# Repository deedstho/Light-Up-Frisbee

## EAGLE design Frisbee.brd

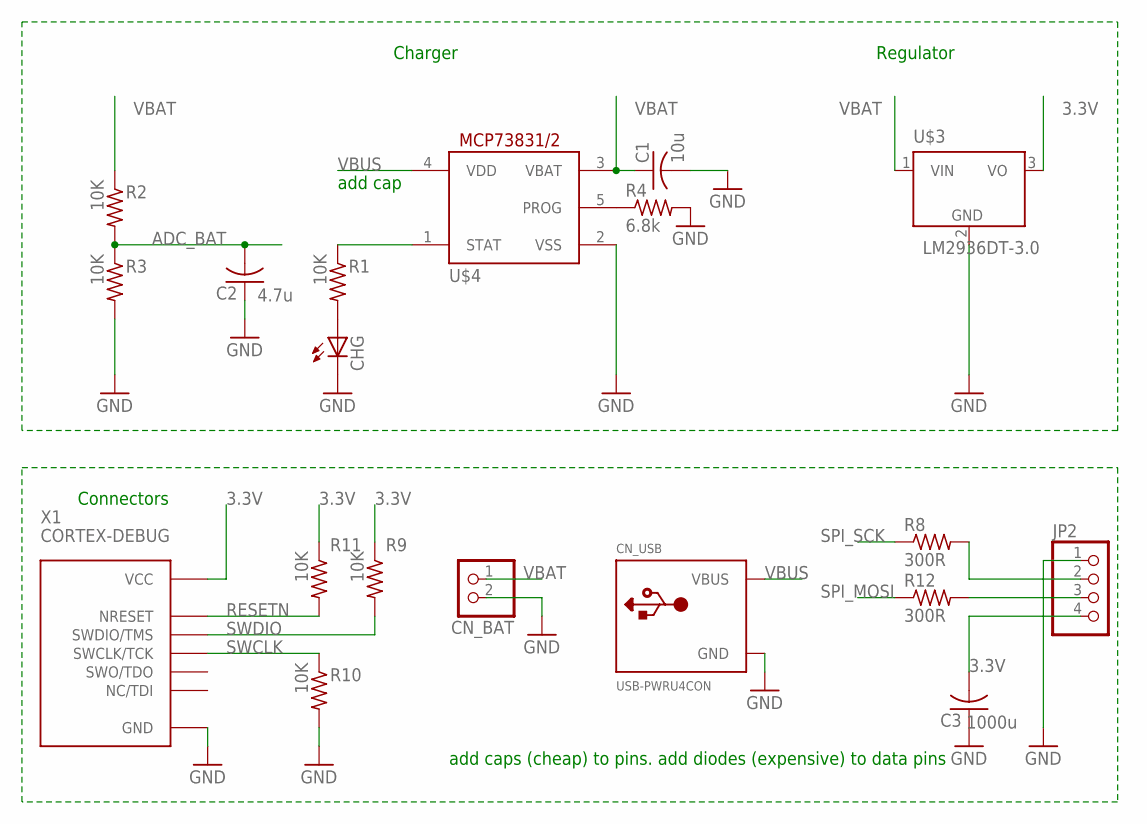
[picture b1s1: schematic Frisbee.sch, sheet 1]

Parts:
C1: 10u; C0805
C2: 4.7u; C0805
C3: 1000u; C0805
CHG: LEDCHIP-LED0603; CHIP-LED0603
CN_BAT: JST_2PIN-SMT-RA; JST-PH-2-SMT-RA
CN_USB: USB-PWRU4CON; USB-MINIB-THM-PWRONLY
JP2: PINHD-1X4/90; 1X04/90
R1, R2, R3, R9, R10, R11: 10K; R0603
R4: 6.8k; R0805
R8, R12: 300R; R0805
U$3: LM2936DT-3.0; TO252
U$4: MCP73831/OT; SOT23-5L
X1: CORTEX-DEBUG

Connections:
3.3V: C3.2, JP2.4, R9.1, R11.1, U$3.3 (VO), X1.VCC; also elsewhere on the board
ADC_BAT: C2.2, R2.2, R3.1; also elsewhere on the board
GND: C1.2, C2.1, C3.1, CHG.C, CN_BAT.2 (1), CN_USB.GND, JP2.1, R3.2, R4.2, R10.2, U$3.2 (GND), U$4.2 (VSS), X1.GND1 (GND), X1.GND2 (GND), X1.GND_DETECT (GND); also elsewhere on the board
unnamed: CHG.A, R1.2
unnamed: R1.1, U$4.1 (STAT)
unnamed: R4.1, U$4.5 (PROG)
unnamed: JP2.3, R12.2
unnamed: JP2.2, R8.2
RESETN: R11.2, X1.NRESET; also elsewhere on the board
SPI_MOSI: R12.1; also elsewhere on the board
SPI_SCK: R8.1; also elsewhere on the board
SWCLK: R10.1, X1.SWCLK/TCK; also elsewhere on the board
SWDIO: R9.2, X1.SWDIO/TMS; also elsewhere on the board
VBAT: C1.1, CN_BAT.1 (2), R2.1, U$3.1 (VIN), U$4.3 (VBAT)
VBUS: CN_USB.VBUS, U$4.4 (VDD)

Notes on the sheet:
Connectors
add cap
add caps (cheap) to pins. add diodes (expensive) to data pins
Charger
Regulator

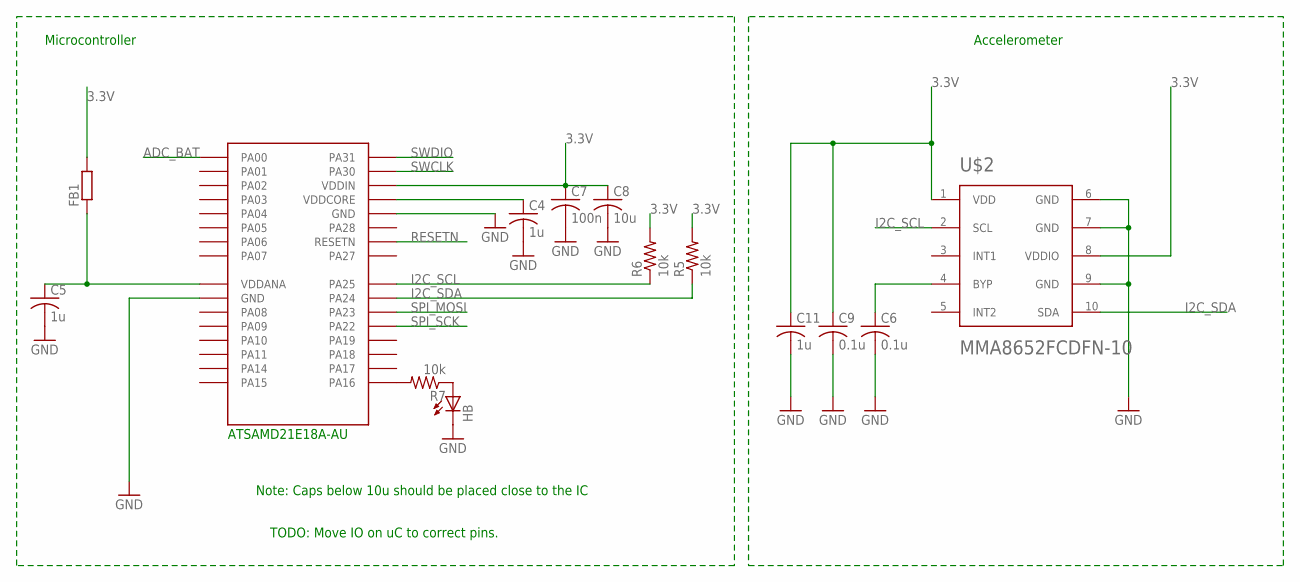
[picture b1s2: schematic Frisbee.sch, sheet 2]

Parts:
C4, C5, C11: 1u; C0603
C6, C9: 0.1u; C0603
C7: 100n; C0603
C8: 10u; C0603
FB1: R-EU_M0805; M0805
HB: LEDCHIPLED_0603; CHIPLED_0603
R5, R6, R7: 10k; R0603
U$1: ATSAMD21E18A-AU; 32-TQFP
U$2: MMA8652FCDFN-10; DFN-10

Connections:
3.3V: C7.1, C8.1, C9.1, C11.1, FB1.2, R5.2, R6.2, U$1.30 (VDDIN), U$2.1 (VDD), U$2.8 (VDDIO); also elsewhere on the board
ADC_BAT: U$1.1 (PA00); also elsewhere on the board
GND: C4.2, C5.2, C6.2, C7.2, C8.2, C9.2, C11.2, HB.C, U$1.10 (GND), U$1.28 (GND), U$2.6 (GND), U$2.7 (GND), U$2.9 (GND); also elsewhere on the board
I2C_SCL: R6.1, U$1.24 (PA25), U$2.2 (SCL)
I2C_SDA: R5.1, U$1.23 (PA24), U$2.10 (SDA)
unnamed: C4.1, U$1.29 (VDDCORE)
unnamed: R7.2, U$1.17 (PA16)
unnamed: HB.A, R7.1
unnamed: C6.1, U$2.4 (BYP)
NOT3.3: C5.1, FB1.1, U$1.9 (VDDANA)
RESETN: U$1.26 (RESETN); also elsewhere on the board
SPI_MOSI: U$1.22 (PA23); also elsewhere on the board
SPI_SCK: U$1.21 (PA22); also elsewhere on the board
SWCLK: U$1.31 (PA30); also elsewhere on the board
SWDIO: U$1.32 (PA31); also elsewhere on the board

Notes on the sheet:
Microcontroller
Accelerometer
ATSAMD21E18A-AU
TODO: Move IO on uC to correct pins.
Note: Caps below 10u should be placed close to the IC

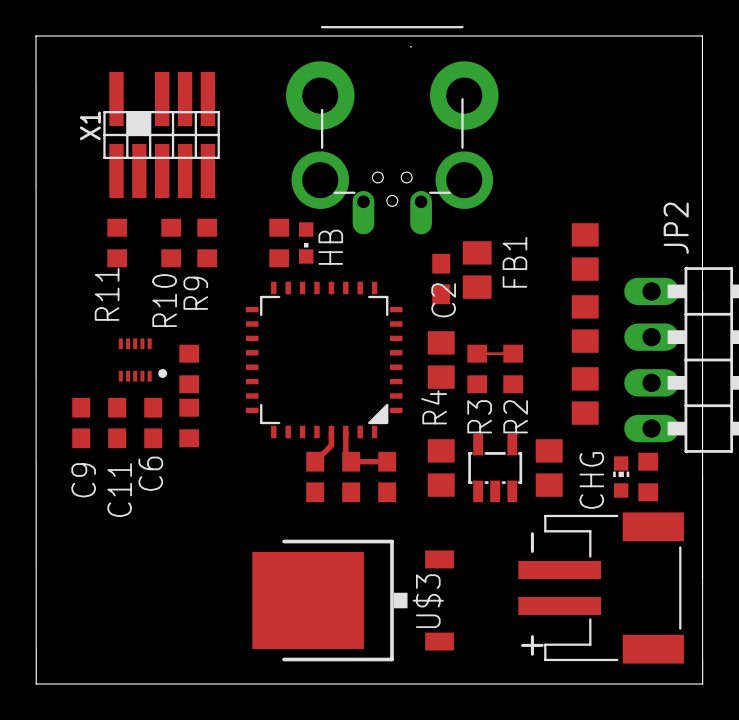
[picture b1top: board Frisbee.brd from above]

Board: 2 copper layers, 37.0 x 36.0 mm, 33 parts (0 on the bottom side), 22 nets.

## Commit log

2019-12-28 initial commit. schematicand layout. Routing not complete.
